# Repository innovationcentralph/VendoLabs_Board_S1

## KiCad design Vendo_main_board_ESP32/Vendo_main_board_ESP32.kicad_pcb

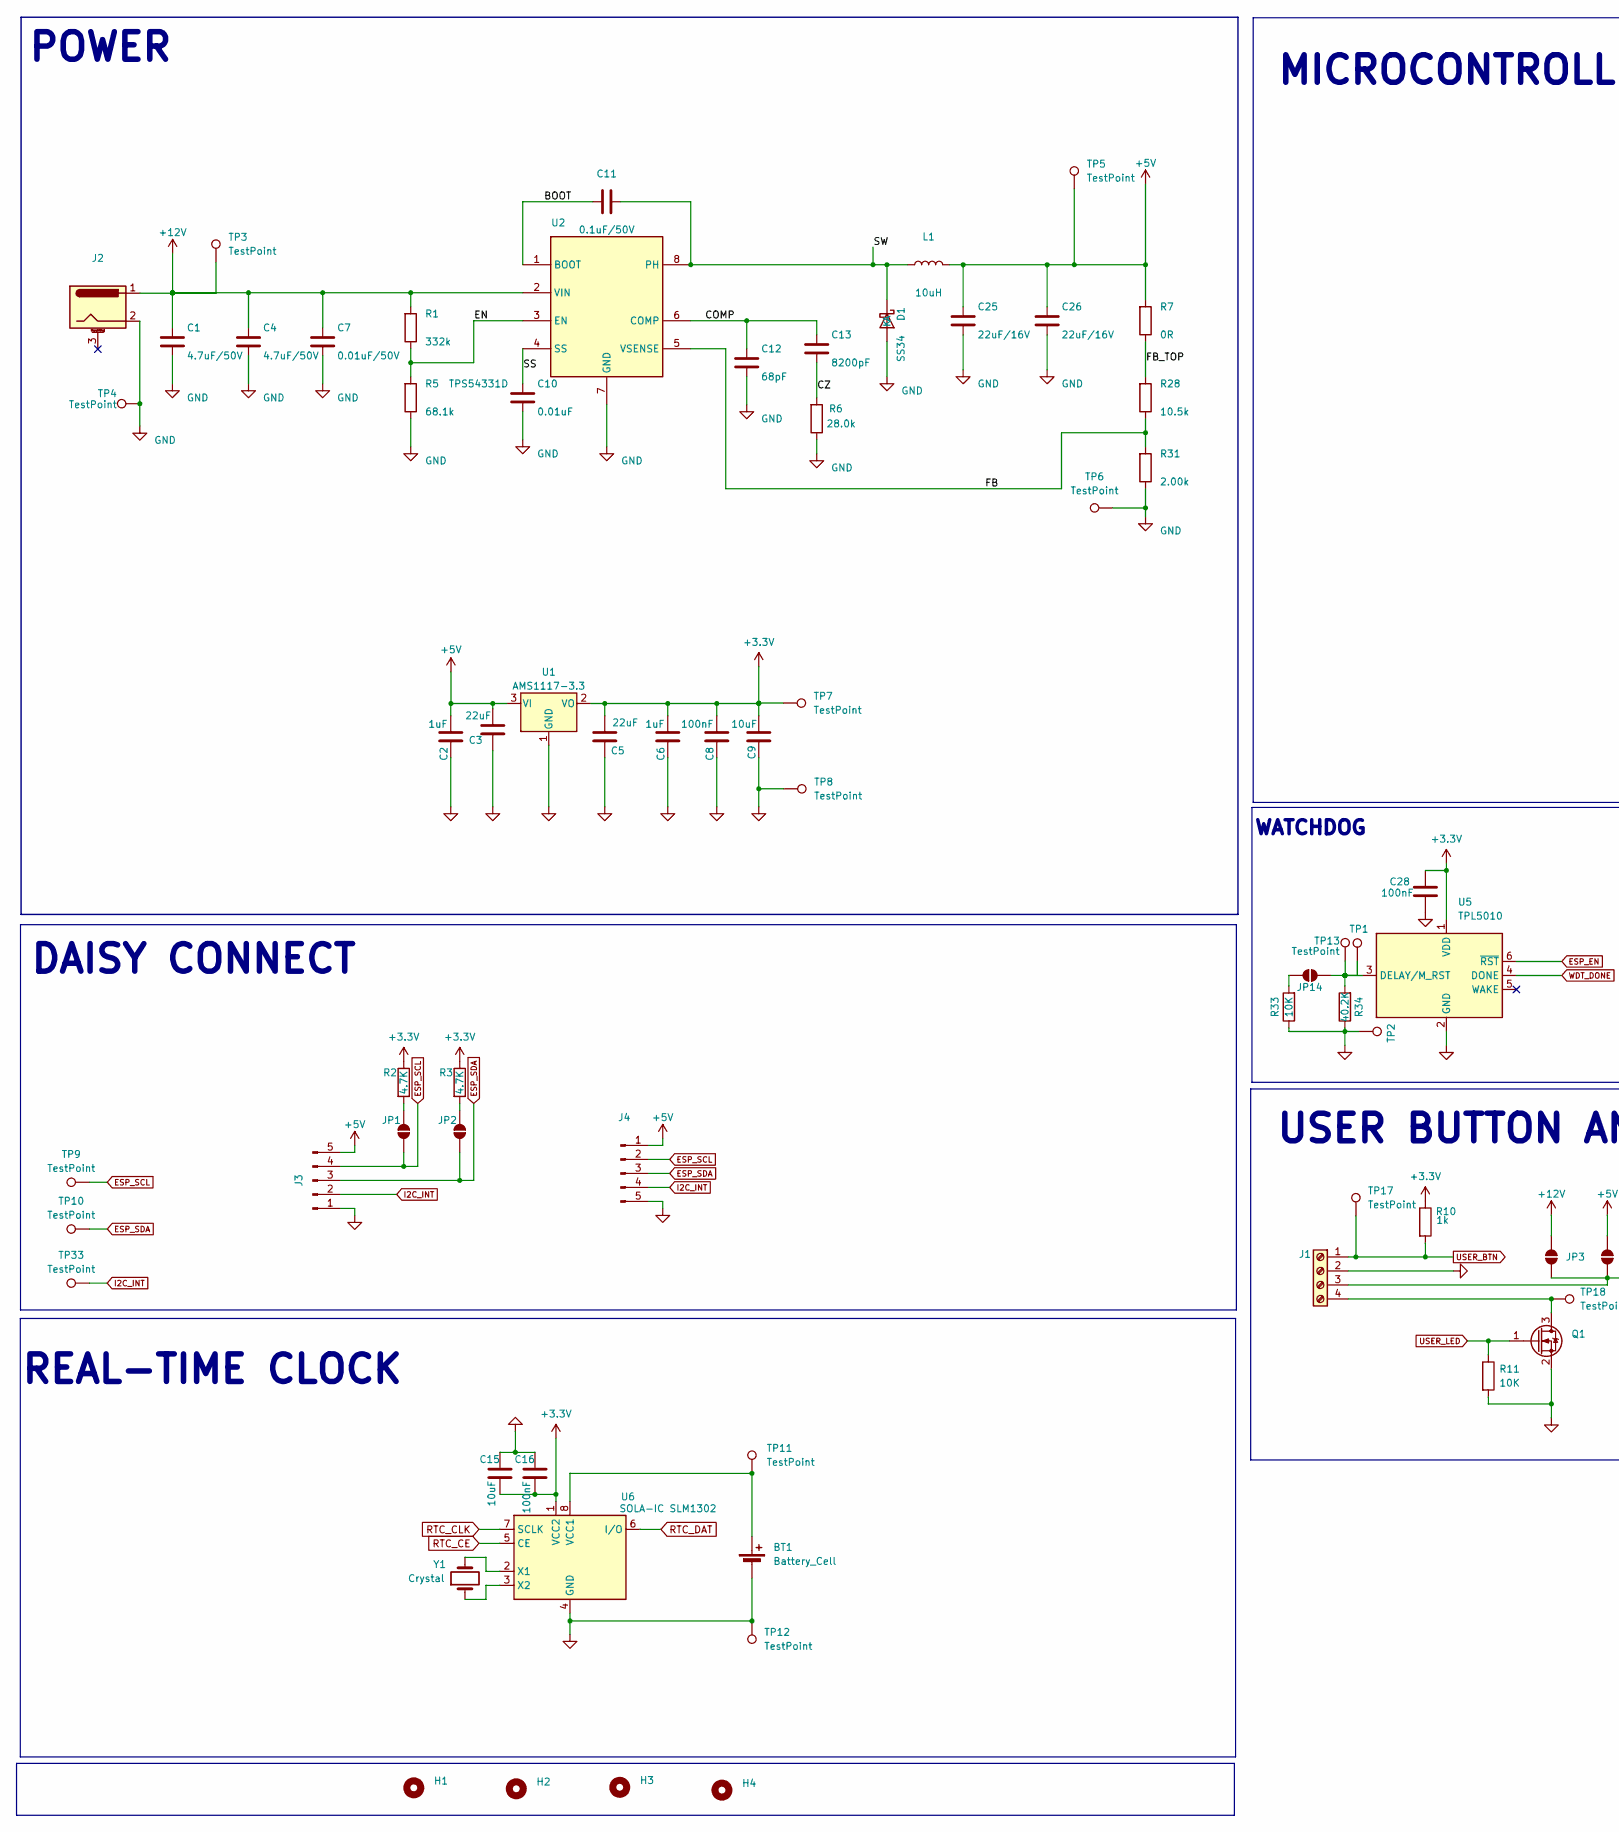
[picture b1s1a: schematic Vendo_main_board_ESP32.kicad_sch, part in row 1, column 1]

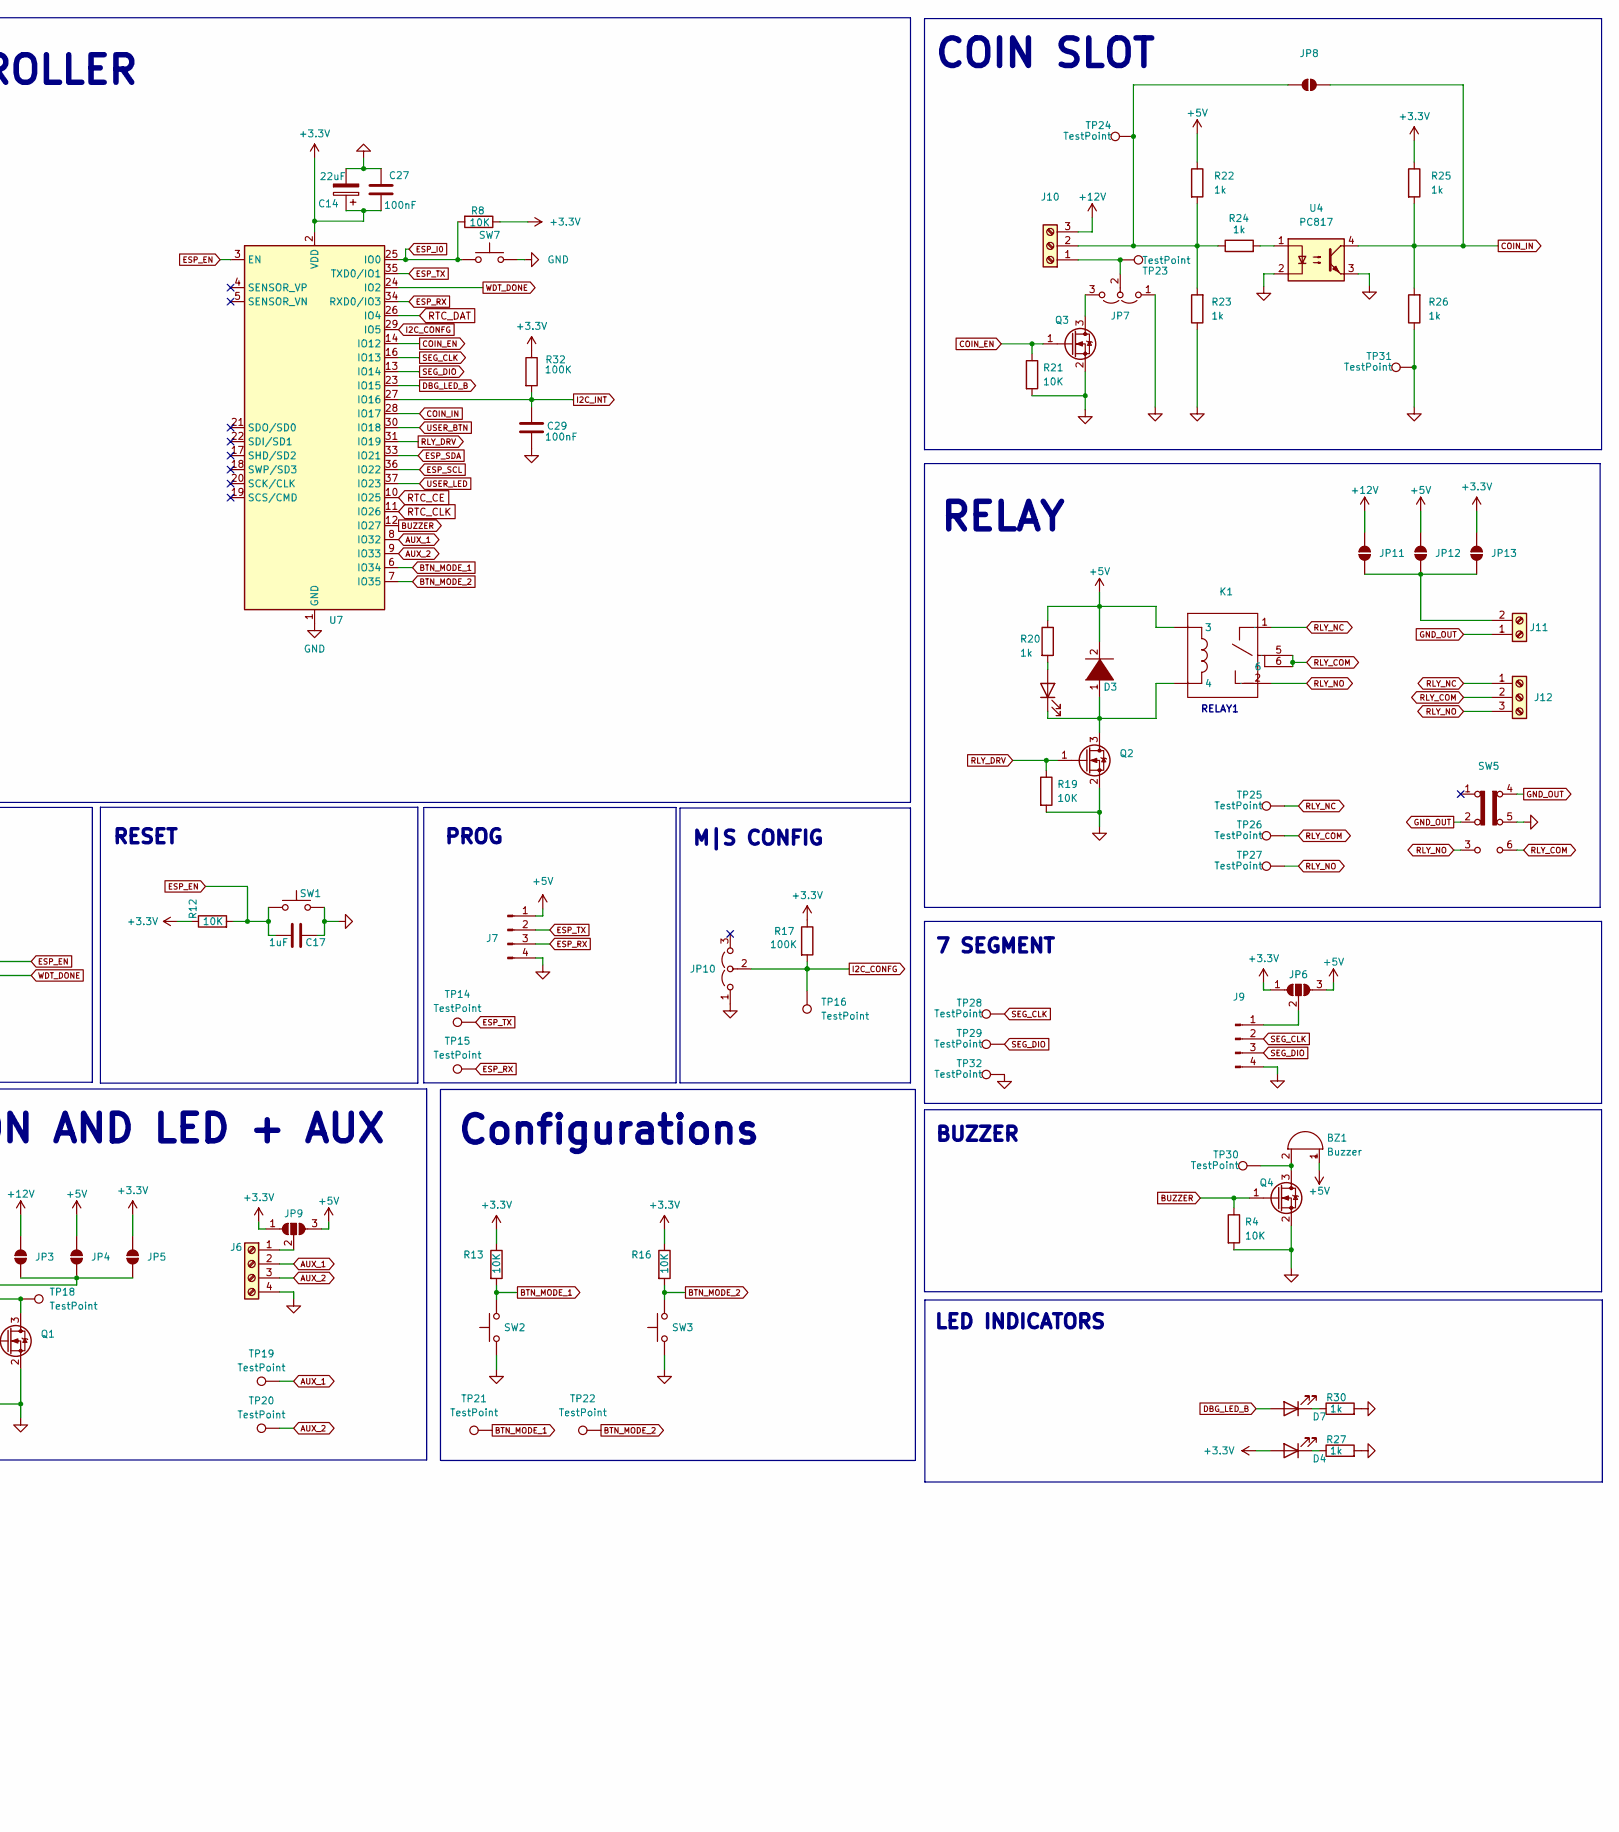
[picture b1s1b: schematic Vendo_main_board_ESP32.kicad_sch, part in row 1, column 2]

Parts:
BT1: Battery_Cell; BAT-TH_CR2032-BS-6-1; LCSC C969909
BZ1: Buzzer; Buzzer_12x9.5RM7.6
C1, C4: 4.7uF/50V; C_1206_3216Metric; MPN FH 1206B475K500NT; LCSC C29823
C2, C6: 1uF; C_0805_2012Metric_Pad1.18x1.45mm_HandSolder; LCSC C49678
C3, C5: 22uF; C_0603_1608Metric; LCSC C59461
C7: 0.01uF/50V; C_0603_1608Metric; MPN Samsung CL10B103KB8NNNC; LCSC C1589
C8, C16, C27, C28, C29: 100nF; C_0603_1608Metric_Pad1.08x0.95mm_HandSolder; LCSC C14663
C9: 10uF; C_0603_1608Metric_Pad1.08x0.95mm_HandSolder; LCSC C85713
C10: 0.01uF; C_0603_1608Metric; MPN Samsung CL10B103KB8NNNC; LCSC C1589
C11: 0.1uF/50V; C_0603_1608Metric; MPN Samsung CL10B104KB8NNNC; LCSC C1591
C12: 68pF; C_0603_1608Metric; MPN FH 0603CG680J500NT; LCSC C1680
C13: 8200pF; C_0603_1608Metric; MPN FH 0603B822K500NT; LCSC C1322360
C14: 22uF; C_0603_1608Metric_Pad1.08x0.95mm_HandSolder; LCSC C59461
C15: 10uF; C_0603_1608Metric_Pad1.08x0.95mm_HandSolder; LCSC C19702
C17: 1uF; C_0603_1608Metric_Pad1.08x0.95mm_HandSolder; LCSC C14663
C25, C26: 22uF/16V; C_1210_3225Metric; MPN Samsung CL32B226KOJNNNE; LCSC C55530
D1: SS34; D_SMA; MPN R+O SS34; LCSC C7420365
D2, D4, D7: LED; LED_0805_2012Metric_Pad1.15x1.40mm_HandSolder; LCSC C2297
D3: 1N4001; D_SOD-123F; LCSC C2892326
H1, H2, H3, H4: MountingHole; MountingHole_3.2mm_M3_DIN965_Pad_TopBottom
J1, J6: Screw_Terminal_01x04; TerminalBlock_Xinya_XY308-2.54-4P_1x04_P2.54mm_Horizontal
J2: Barrel_Jack_MountingPin; BarrelJack_GCT_DCJ200-10-A_Horizontal
J3, J4: Conn_01x05_Pin; JST_EH_B5B-EH-A_1x05_P2.50mm_Vertical
J7: FTDI; PinHeader_1x04_P2.54mm_Vertical
J9: Conn_01x04_Pin; JST_EH_B4B-EH-A_1x04_P2.50mm_Vertical
J10: Screw_Terminal_01x03; TerminalBlock_Xinya_XY308-2.54-3P_1x03_P2.54mm_Horizontal
J11: Screw_Terminal_01x02; TerminalBlock_MetzConnect_Type073_RT02602HBLU_1x02_P5.08mm_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
J12: Screw_Terminal_01x03; TerminalBlock_MetzConnect_Type073_RT02603HBLU_1x03_P5.08mm_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
JP1, JP2, JP8: SolderJumper_2_Open; SolderJumper-2_P1.3mm_Open_RoundedPad1.0x1.5mm
JP3, JP4, JP5, JP11, JP12, JP13: SolderJumper_2_Open; PinHeader_1x02_P2.54mm_Vertical
JP6, JP9: SolderJumper_3_Open; SolderJumper-3_P1.3mm_Open_Pad1.0x1.5mm_NumberLabels
JP7, JP10: Jumper_3_Open; PinHeader_1x03_P2.54mm_Vertical
JP14: SolderJumper_2_Open; SolderJumper-2_P1.3mm_Open_Pad1.0x1.5mm
K1: RELAY-TH_SLA-XXVDC-SL-C; Manufacturer Part SLA-5VDC-SL-C; LCSC Part Name 5V继电器 单刀双掷
L1: 10uH; IND-SMD_L11.5-W10.0_FXL1040; MPN cjiang FXL1040-100-M; LCSC C475915
Q1, Q2, Q3, Q4: Q_NMOS_Depletion_GSD; SOT-23-3; LCSC C75882
R1: 332k; R_0603_1608Metric; MPN UNI-ROYAL 0603WAF3323T5E; LCSC C23139
R2, R3: 4.7K; R_0603_1608Metric_Pad0.98x0.95mm_HandSolder; LCSC C2960810
R4, R11, R19, R21: 10K; R_0805_2012Metric_Pad1.20x1.40mm_HandSolder; LCSC C2930231
R5: 68.1k; R_0603_1608Metric; MPN UNI-ROYAL 0603WAF6812T5E; LCSC C25976
R6: 28.0k; R_0603_1608Metric; MPN UNI-ROYAL 0603WAF2802T5E; LCSC C22989
R7: 0R; R_0603_1608Metric; MPN YAGEO RC0603JR-070RL; LCSC C95177
R8, R12, R13, R16: 10K; R_0603_1608Metric_Pad0.98x0.95mm_HandSolder; LCSC C21190
R10, R20, R22, R23, R24, R25, R26, R27, R30: 1k; R_0603_1608Metric_Pad0.98x0.95mm_HandSolder; LCSC C21190
R17: 100K; R_0603_1608Metric_Pad0.98x0.95mm_HandSolder; LCSC C21190
R28: 10.5k; R_0603_1608Metric; MPN FOJAN FRC0603F1052TS; LCSC C2933127
R31: 2.00k; R_0603_1608Metric; MPN YAGEO RC0603FR-072KL; LCSC C105576
R32: 100K; R_0603_1608Metric_Pad0.98x0.95mm_HandSolder; LCSC C105574
R33: 10K; R_0603_1608Metric_Pad0.98x0.95mm_HandSolder; LCSC C2906982
R34: 40.2K; R_0603_1608Metric_Pad0.98x0.95mm_HandSolder; LCSC C12447
SW1: SW_Push; SW_SPST_PTS645; LCSC C2689642
SW2, SW3: SW_Push; SW_SPST_PTS645
SW5: SW_Slide_DPDT; DPDT_PUSH
SW7: SW_Push; PinHeader_1x02_P2.54mm_Vertical; LCSC C2689642
TP1, TP2, TP14, TP15, TP28, TP29: TestPoint; TestPoint_Pad_D1.5mm
TP3, TP4, TP5, TP6, TP7, TP8, TP9, TP10, TP11, TP12, TP13, TP16, TP17, TP18, TP19, TP20, TP21, TP22, TP23, TP24, TP25, TP26, TP27, TP30, TP31, TP32, TP33: TestPoint; TestPoint_Pad_D2.5mm
U1: AMS1117-3.3; SOT-223-3_TabPin2; LCSC C5199435
U2: TPS54331D; SOIC-8_3.9x4.9mm_P1.27mm; MPN TPS54331DR; LCSC C9865
U4: PC817; APC-817xx-SL_AMB; LCSC C66405
U5: TPL5010; SOT-23-6; LCSC C473912
U6: SOLA-IC SLM1302; SOIC-8_3.9x4.9mm_P1.27mm; LCSC C125188
U7: ESP32-WROOM-32; ESP32-WROOM-32UE; LCSC C529577
Y1: Crystal; OSC-SMD_L3.2-W1.5; LCSC C97606

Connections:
+3.3V: C5.2, C6.2, C8.2, C9.2, C14.1, C15.1, C16.1, C27.1, C28.1, D4.2 (A), JP5.2 (B), JP6.1 (A), JP9.1 (A), JP13.2 (B), R2.1, R3.1, R8.1, R10.1, R12.1, R13.1, R16.1, R17.1, R25.1, R32.1, TP7.1, U1.2 (VO), U5.1 (VDD), U6.1 (VCC2), U7.2 (VDD)
+5V: BZ1.1 (+), C2.2, C3.2, C25.1, C26.1, D3.2 (A), J3.5, J4.1, J7.1, JP4.2 (B), JP6.3 (B), JP9.3 (B), JP12.2 (B), K1.3, L1.2, R7.1, R20.1, R22.1, TP5.1, U1.3 (VI)
+12V: C1.1, C4.1, C7.1, J2.1, J10.3, JP3.2 (B), JP11.2 (B), R1.1, TP3.1, U2.2 (VIN)
/BOOT: C11.1, U2.1 (BOOT)
/COMP: C12.1, C13.1, U2.6 (COMP)
/CZ: C13.2, R6.1
/EN: R1.2, R5.1, U2.3 (EN)
/FB: R28.2, R31.1, U2.5 (VSENSE)
/FB_TOP: R7.2, R28.1
/SS: C10.1, U2.4 (SS)
/SW: C11.2, D1.1 (K), L1.1, U2.8 (PH)
AUX_1: J6.2, TP19.1, U7.8 (IO32)
AUX_2: J6.3, TP20.1, U7.9 (IO33)
BTN_MODE_1: R13.2, SW2.2, TP21.1, U7.6 (IO34)
BTN_MODE_2: R16.2, SW3.2, TP22.1, U7.7 (IO35)
BUZZER: Q4.1 (G), R4.1, U7.12 (IO27)
COIN_EN: Q3.1 (G), R21.1, U7.14 (IO12)
COIN_IN: JP8.2 (B), R25.2, R26.2, U4.4, U7.28 (IO17)
DBG_LED_B: D7.2 (A), U7.23 (IO15)
ESP_EN: C17.2, R12.2, SW1.1, U5.6 (~RST), U7.3 (EN)
ESP_I0: R8.2, SW7.1, U7.25 (IO0)
ESP_RX: J7.3, TP15.1, U7.34 (RXD0/IO3)
ESP_SCL: J3.4, J4.2, JP1.1 (A), TP9.1, U7.36 (IO22)
ESP_SDA: J3.3, J4.3, JP2.1 (A), TP10.1, U7.33 (IO21)
ESP_TX: J7.2, TP14.1, U7.35 (TXD0/IO1)
GND: BT1.2 (-), C1.2, C2.1, C3.1, C4.2, C5.1, C6.1, C7.2, C8.1, C9.1, C10.2, C12.2, C14.2, C15.2, C16.2, C17.1, C25.2, C26.2, C27.2, C28.2, C29.1, D1.2 (A), J1.2, J2.2, J3.1, J4.5, J6.4, J7.4, J9.4, JP7.1 (A), JP10.1 (A), Q1.2 (S), Q2.2 (S), Q3.2 (S), Q4.2 (S), R4.2, R5.2, R6.2, R11.2, R19.2, R21.2, R23.1, R26.1, R27.2, R30.2, R31.2, R33.1, R34.1, SW1.2, SW2.1, SW3.1, SW5.5 (B), SW7.2, TP2.1, TP4.1, TP6.1, TP8.1, TP12.1, TP31.1, TP32.1, U1.1 (GND), U2.7 (GND), U4.2, U4.3, U5.2 (GND), U6.4 (GND), U7.1 (GND), U7.15 (GND), U7.38 (GND), U7.39 (GND)
GND_OUT: J11.1, SW5.2 (B), SW5.4 (C)
I2C_CONFG: JP10.2 (C), R17.2, TP16.1, U7.29 (IO5)
I2C_INT: C29.2, J3.2, J4.4, R32.2, TP33.1, U7.27 (IO16)
unnamed: BT1.1 (+), TP11.1, U6.8 (VCC1)
unnamed: BZ1.2 (-), Q4.3 (D), TP30.1
unnamed: D2.2 (A), R20.2
unnamed: D2.1 (K), D3.1 (K), K1.4, Q2.3 (D)
unnamed: D4.1 (K), R27.1
unnamed: D7.1 (K), R30.1
unnamed: J1.3, JP3.1 (A), JP4.1 (A), JP5.1 (A)
unnamed: J1.4, Q1.3 (D), TP18.1
unnamed: J6.1, JP9.2 (C)
unnamed: J9.1, JP6.2 (C)
unnamed: J10.1, JP7.2 (C), TP23.1
unnamed: J10.2, JP8.1 (A), R22.2, R23.2, R24.1, TP24.1
unnamed: J11.2, JP11.1 (A), JP12.1 (A), JP13.1 (A)
unnamed: JP1.2 (B), R2.2
unnamed: JP2.2 (B), R3.2
unnamed: JP7.3 (B), Q3.3 (D)
unnamed: JP14.1 (A), R33.2
unnamed: JP14.2 (B), R34.2, TP1.1, TP13.1, U5.3 (DELAY/M_RST)
unnamed: R24.2, U4.1
unnamed: U6.2 (X1), Y1.2
unnamed: U6.3 (X2), Y1.1
RLY_COM: J12.2, K1.5, K1.6, SW5.6 (A), TP26.1
RLY_DRV: Q2.1 (G), R19.1, U7.31 (IO19)
RLY_NC: J12.1, K1.1, TP25.1
RLY_NO: J12.3, K1.2, SW5.3 (C), TP27.1
RTC_CE: U6.5 (CE), U7.10 (IO25)
RTC_CLK: U6.7 (SCLK), U7.11 (IO26)
RTC_DAT: U6.6 (I/O), U7.26 (IO4)
SEG_CLK: J9.2, TP28.1, U7.16 (IO13)
SEG_DIO: J9.3, TP29.1, U7.13 (IO14)
USER_BTN: J1.1, R10.2, TP17.1, U7.30 (IO18)
USER_LED: Q1.1 (G), R11.1, U7.37 (IO23)
WDT_DONE: U5.4 (DONE), U7.24 (IO2)

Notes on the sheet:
DAISY CONNECT
WATCHDOG
USER BUTTON AND LED + AUX
COIN SLOT
M|S CONFIG
RESET
POWER
7 SEGMENT
RELAY1
Configurations
PROG
RELAY
MICROCONTROLLER
REAL-TIME CLOCK
BUZZER
LED INDICATORS

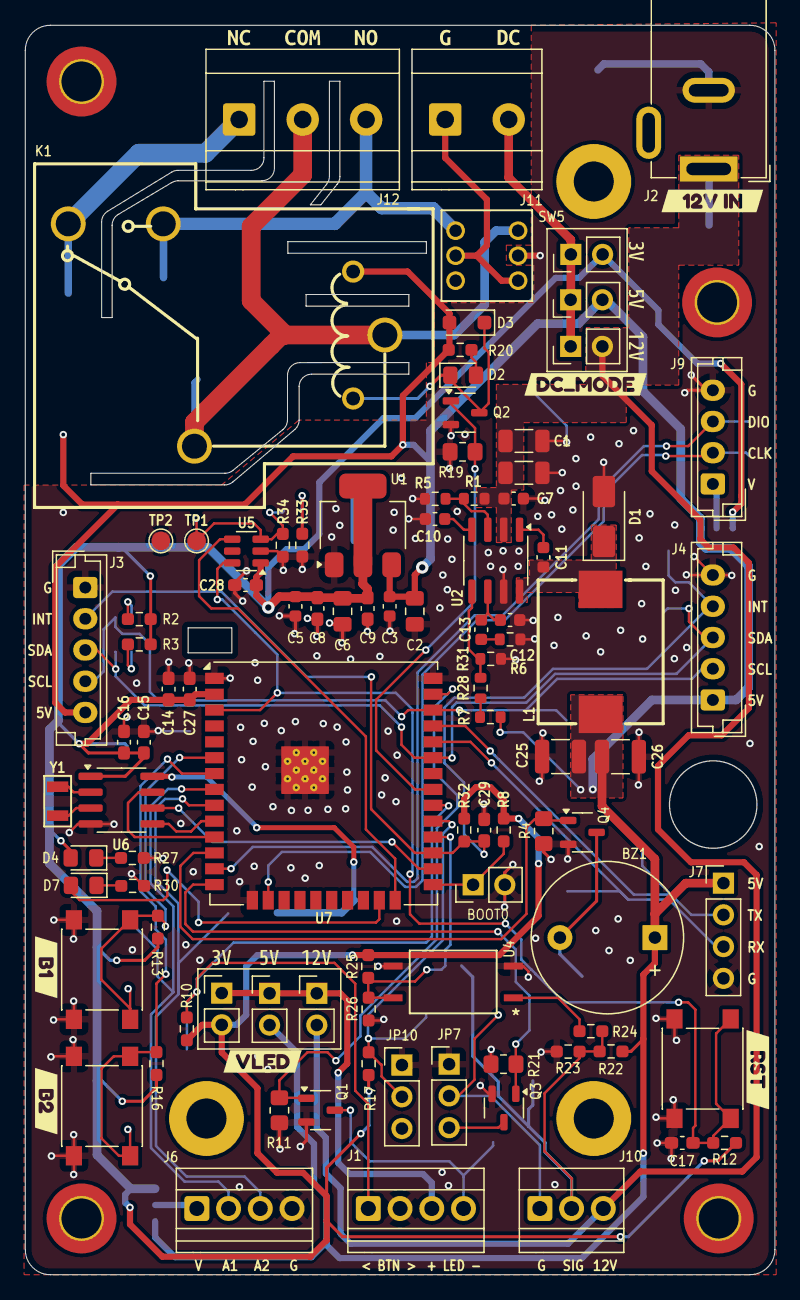
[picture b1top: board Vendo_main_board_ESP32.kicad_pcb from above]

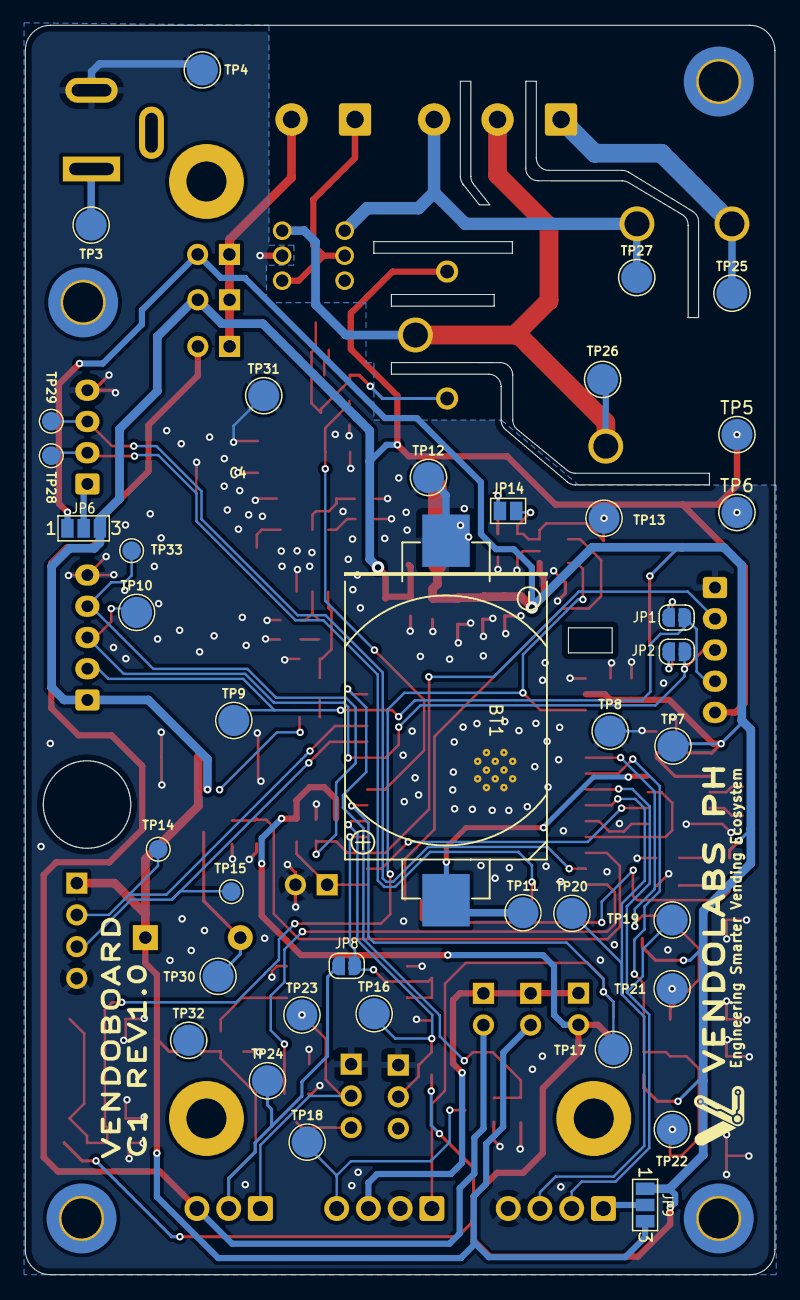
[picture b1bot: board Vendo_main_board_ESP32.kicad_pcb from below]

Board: 2 copper layers, 60.0 x 100.0 mm, 154 parts (38 on the bottom side), 62 nets.

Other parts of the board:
kibuzzard-6A0C4EC9: G***; kibuzzard-6A0C4EC9
kibuzzard-6A0C4ED1: G***; kibuzzard-6A0C4ED1
kibuzzard-6A0C4EDA: G***; kibuzzard-6A0C4EDA
kibuzzard-6A0C4EE4: G***; kibuzzard-6A0C4EE4
kibuzzard-6A0C5E83, kibuzzard-6A0C5E83#2: G***; kibuzzard-6A0C5E83
kibuzzard-6A0C5E89, kibuzzard-6A0C5E89#2: G***; kibuzzard-6A0C5E89
kibuzzard-6A0C5E92, kibuzzard-6A0C5E92#2: G***; kibuzzard-6A0C5E92
kibuzzard-6A0C5F1E: G***; kibuzzard-6A0C5F1E
kibuzzard-6A0C57A3: G***; kibuzzard-6A0C57A3
kibuzzard-6A0C57A8: G***; kibuzzard-6A0C57A8
kibuzzard-6A0C536D: G***; kibuzzard-6A0C536D
kibuzzard-6A0C5003: G***; kibuzzard-6A0C5003
kibuzzard-6A561C38: G***; kibuzzard-6A561C38
kibuzzard-6A563CE9: G***; kibuzzard-6A563CE9

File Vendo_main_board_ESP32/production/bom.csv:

Designator,Footprint,Quantity,Value,LCSC Part #
BT1,BAT-TH_CR2032-BS-6-1,1,Battery_Cell,C969909
BZ1,Buzzer_12x9.5RM7.6,1,Buzzer,
"C1, C4",1206,2,4.7uF/50V,C29823
C10,0603,1,0.01uF,C1589
C11,0603,1,0.1uF/50V,C1591
C12,0603,1,68pF,C1680
C13,0603,1,8200pF,C1322360
"C14, C3, C5",0603,3,22uF,C59461
C15,0603,1,10uF,C19702
"C16, C27, C28, C29, C8",0603,5,100nF,C14663
C17,0603,1,1uF,C14663
"C2, C6",0805,2,1uF,C49678
"C25, C26",1210,2,22uF/16V,C55530
C7,0603,1,0.01uF/50V,C1589
C9,0603,1,10uF,C85713
D1,D_SMA,1,SS34,C7420365
"D2, D4, D7",0805,3,LED,C2297
D3,D_SOD-123F,1,1N4001,C2892326
"J1, J6",TerminalBlock_Xinya_XY308-2.54-4P_1x04_P2.54mm_Horizontal,2,Screw_Terminal_01x04,
J10,TerminalBlock_Xinya_XY308-2.54-3P_1x03_P2.54mm_Horizontal,1,Screw_Terminal_01x03,
J11,TerminalBlock_MetzConnect_Type073_RT02602HBLU_1x02_P5.08mm_Horizontal,1,Screw_Terminal_01x02,
J12,TerminalBlock_MetzConnect_Type073_RT02603HBLU_1x03_P5.08mm_Horizontal,1,Screw_Terminal_01x03,
J2,BarrelJack_GCT_DCJ200-10-A_Horizontal,1,Barrel_Jack_MountingPin,
"J3, J4",JST_EH_B5B-EH-A_1x05_P2.50mm_Vertical,2,Conn_01x05_Pin,
J7,PinHeader_1x04_P2.54mm_Vertical,1,FTDI,
J9,JST_EH_B4B-EH-A_1x04_P2.50mm_Vertical,1,Conn_01x04_Pin,
"JP1, JP2, JP8",SolderJumper-2_P1.3mm_Open_RoundedPad1.0x1.5mm,3,SolderJumper_2_Open,
"JP11, JP12, JP13, JP3, JP4, JP5",PinHeader_1x02_P2.54mm_Vertical,6,SolderJumper_2_Open,
JP14,SolderJumper-2_P1.3mm_Open_Pad1.0x1.5mm,1,SolderJumper_2_Open,
K1,RELAY-TH_SLA-XXVDC-SL-C,1,~,
L1,IND-SMD_L11.5-W10.0_FXL1040,1,10uH,C475915
"Q1, Q2, Q3, Q4",SOT-23-3,4,Q_NMOS_Depletion_GSD, C75882
R1,0603,1,332k,C23139
"R10, R20, R22, R23, R24, R25, R26, R27, R30",0603,9,1K,C21190
"R11, R19, R21, R4",0805,4,10K,C2930231
"R12, R13, R16, R8",0603,4,10K,C21190
R17,0603,1,100K,C21190
"R2, R3",0603,2,4.7K,C2960810
R28,0603,1,10.5k,C2933127
R31,0603,1,2.00k,C105576
R32,0603,1,100K,C105574
R33,0603,1,10K,C2906982
R34,0603,1,40.2K,C12447
R5,0603,1,68.1k,C25976
R6,0603,1,28.0k,C22989
R7,0603,1,0R,C95177
SW1,SW_SPST_PTS645,1,SW_Push,C2689642
"SW2, SW3",SW_SPST_PTS645,2,SW_Push,
SW5,DPDT_PUSH,1,SW_Slide_DPDT,
SW7,PinHeader_1x02_P2.54mm_Vertical,1,SW_Push,C2689642
"TP1, TP2",TestPoint_Pad_D1.5mm,2,TestPoint,
U1,SOT-223-3_TabPin2,1,AMS1117-3.3,C5199435
U2,SOIC-8_3.9x4.9mm_P1.27mm,1,TPS54331D,C9865
U4,APC-817xx-SL_AMB,1,PC817,C66405
U5,SOT-23-6,1,TPL5010,C473912
U6,SOIC-8_3.9x4.9mm_P1.27mm,1,SOLA-IC SLM1302,C125188
U7,ESP32-WROOM-32UE,1,ESP32-WROOM-32,C529577
Y1,OSC-SMD_L3.2-W1.5,1,Crystal,C97606
